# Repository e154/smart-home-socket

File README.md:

Автомат управления розетками/нагрузками
---------------------------------------

[Project site](https://e154.github.io/smart-home/) |
[Server](https://github.com/e154/smart-home/) |
[Configurator](https://github.com/e154/smart-home-configurator/) |
[Node](https://github.com/e154/smart-home-node/) |
[Development Tools](https://github.com/e154/smart-home-tools/) |
[Smart home Socket](https://github.com/e154/smart-home-socket/)

##### Функции
    Контроль температуры силового блока
    Включение/Выключения по команде управляющего сервера
    Контроль наличия сети/фазы

##### Общение с сервером
    Общение происходит по линии связи rs485, с помощью модифицированного 
    протокола MODBUS ASCII

##### Поведение автомата

    состояния:
    включен/выключен

    температура:
    в пределах нормы
    за пределами нормы

    комманды консоли:
    запрос состояния
          температура
          фаза
          вкл/выкл
          максимальный предел температуры
    включить
    выключить

##### Список компонентов

    Qty Value            Device                  Package         Parts              Description          
    1                    CPOL-EUE2,5-6E          E2,5-6E         C12                POLARIZED CAPACITOR, 
    1                    LEDCHIPLED_0805         CHIPLED_0805    LED2               LED                  
    5                    M01NOSILK-KIT           1X01NS-KIT      J1, J2, J3, J6, J7 Header 1             
    3                    M01PTH_NO_SILK_YES_STOP 1X01_NO_SILK    J4, J5, TEMP       Header 1             
    1                    MA03-2                  MA03-2          ISP                PIN HEADER           
    4                    MA04-1                  MA04-1          SV1, SV2, SV3, SV5 PIN HEADER           
    1   0.05mF           C-EUC0805               C0805           C6                 CAPACITOR, European  
    5   0.1              C-EUC0805               C0805           C1, C4, C5, C7, C8 CAPACITOR, European  
    2   10K              R-EU_M0805              M0805           R8, R12            RESISTOR, European s 
    3   10K              R-EU_R0805              R0805           R1, R13, R14       RESISTOR, European s 
    1   120R             R-EU_R0805              R0805           R17                RESISTOR, European s 
    1   16MHz            CRYSTALHC49U70          HC49U70         Q1                 CRYSTAL              
    1   1K               R-EU_M0805              M0805           R10                RESISTOR, European s 
    1   1K               R-EU_M1206              M1206           R9                 RESISTOR, European s 
    1   1K               R-EU_R0805              R0805           R2                 RESISTOR, European s 
    2   22p              C-EUC0805               C0805           C2, C3             CAPACITOR, European  
    3   330              R-EU_M0805              M0805           R3, R4, R5         RESISTOR, European s 
    1   560K             R-EU_M0805              M0805           R7                 RESISTOR, European s 
    2   560R             R-EU_R0805              R0805           R15, R16           RESISTOR, European s 
    1   78L05Z           78L05Z                  TO92            IC3                Positive VOLTAGE REG 
    2   82K              R-EU_0309/10            0309/10         R6, R11            RESISTOR, European s 
    1   AZ8-FORM-C       AZ8-FORM-C              AZ8             K1                 MINIATURE PC BOARD R 
    2   BC847            NPNSOT23                SOT-23          T2, T3             NPN TRANSISTOR       
    1   BT138-V          BT138-V                 TO220BV         T1                 TRIAC                
    2   DBDB101G         DBDB101G                DB              B1, B2             Single Phase 1.0 AMP 
    1   F/TMB            F/TMB                   F/TMB           SG1                BUZZER Source: Buerk 
    1   MAX481CSA        MAX481CSA               SO08            IC2                RS485 TRANSEIVER     
    1   MEGA48/88/168-AU MEGA48/88/168-AU        TQFP32-08       IC1                                     
    2   MKDSN1,5/2-5,08  MKDSN1,5/2-5,08         MKDSN1,5/2-5,08 X1, X2             MKDSN 1,5/ 2-5,08 Pr 
    1   MOC3031M         MOC3031M                DIL06           OK2                6-Pin DIP Zero-Cross 
    2   PC817            PC817                   DIL04           OK1, OK3           SHARP OPTO COUPLER   

##### Фоты

#### LICENSE

Smart home socket is licensed under the [MIT License (MIT)](https://github.com/e154/smart-home-socket/blob/master/LICENSE).

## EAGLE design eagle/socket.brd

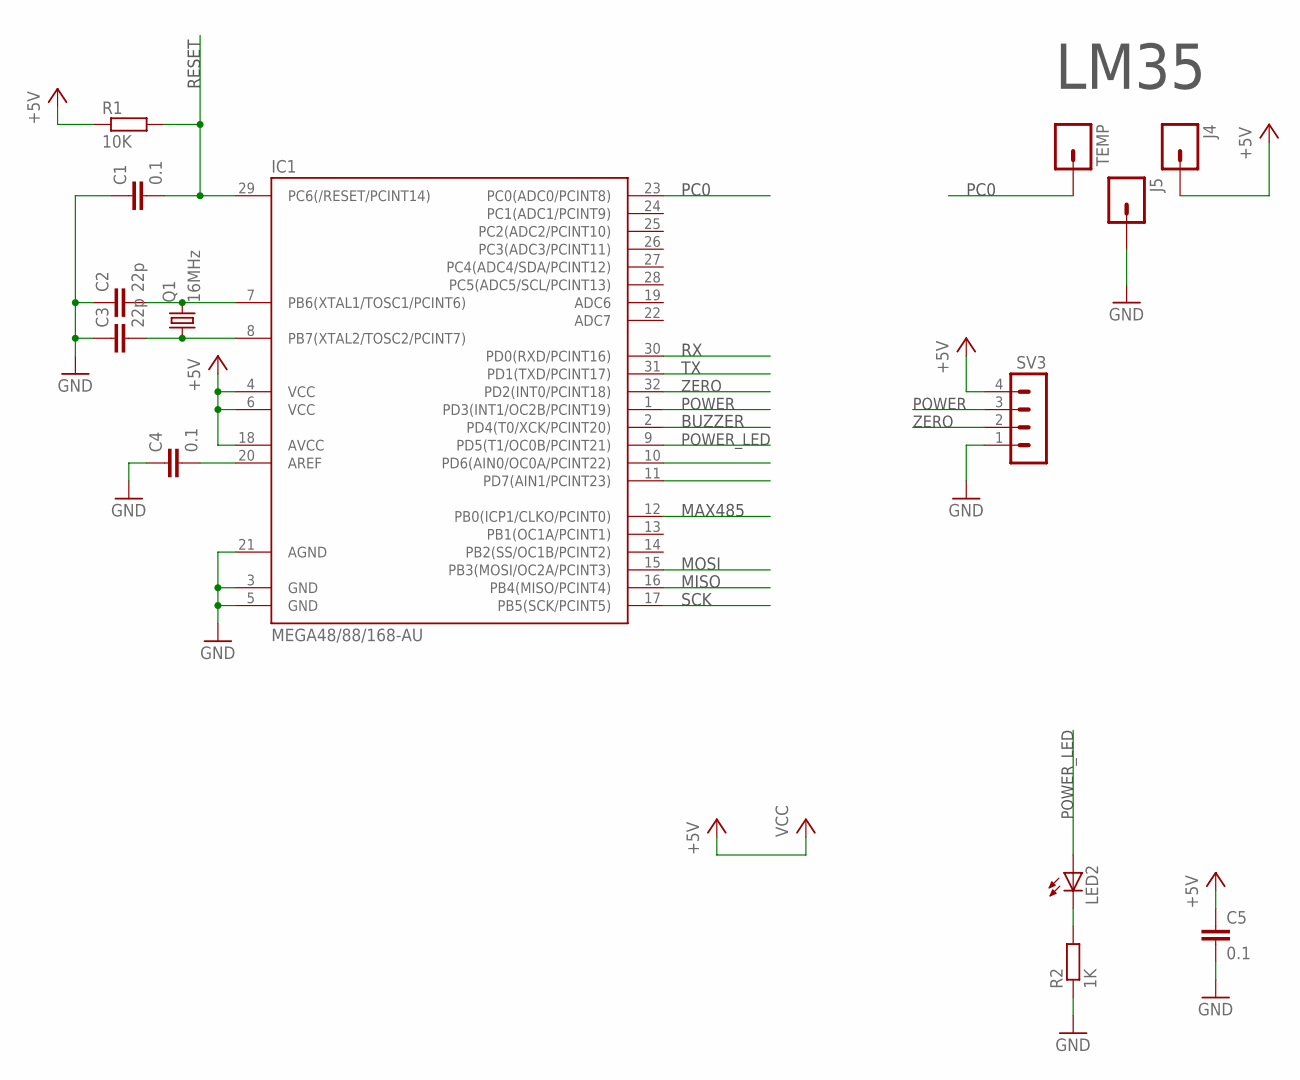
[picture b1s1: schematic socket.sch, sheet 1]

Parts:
C1, C4, C5: 0.1; C0805
C2, C3: 22p; C0805
IC1: MEGA48/88/168-AU; TQFP32-08
J4, J5: M01PTH_NO_SILK_YES_STOP; 1X01_NO_SILK
LED2: LEDCHIPLED_0805; CHIPLED_0805
Q1: 16MHz; HC49U70
R1: 10K; R0805
R2: 1K; R0805
SV3: MA04-1
TEMP: M01PTH_NO_SILK_YES_STOP; 1X01_NO_SILK

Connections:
+5V: C5.1, IC1.4 (VCC), IC1.6 (VCC), IC1.18 (AVCC), J4.1, R1.1, SV3.4; also elsewhere on the board
BUZZER: IC1.2 (PD4(T0/XCK/PCINT20)); also elsewhere on the board
GND: C1.1, C2.1, C3.1, C4.1, C5.2, IC1.3 (GND), IC1.5 (GND), IC1.21 (AGND), J5.1, R2.1, SV3.1; also elsewhere on the board
MISO: IC1.16 (PB4(MISO/PCINT4)); also elsewhere on the board
MOSI: IC1.15 (PB3(MOSI/OC2A/PCINT3)); also elsewhere on the board
unnamed: C4.2, IC1.20 (AREF)
unnamed: C2.2, IC1.7 (PB6(XTAL1/TOSC1/PCINT6)), Q1.2
unnamed: C3.2, IC1.8 (PB7(XTAL2/TOSC2/PCINT7)), Q1.1
unnamed: LED2.C, R2.2
PB0: IC1.12 (PB0(ICP1/CLKO/PCINT0)); also elsewhere on the board
PC0: IC1.23 (PC0(ADC0/PCINT8)), TEMP.1
PD3: IC1.1 (PD3(INT1/OC2B/PCINT19)), SV3.3
PD4: IC1.32 (PD2(INT0/PCINT18)), SV3.2
POWER_LED: IC1.9 (PD5(T1/OC0B/PCINT21)), LED2.A
RESET: C1.2, IC1.29 (PC6(/RESET/PCINT14)), R1.2; also elsewhere on the board
RX: IC1.30 (PD0(RXD/PCINT16)); also elsewhere on the board
SCK: IC1.17 (PB5(SCK/PCINT5)); also elsewhere on the board
TX: IC1.31 (PD1(TXD/PCINT17)); also elsewhere on the board

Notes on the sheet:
RESET
SCK
MISO
MOSI
MAX485
PC0
BUZZER
POWER
ZERO
LM35
POWER_LED

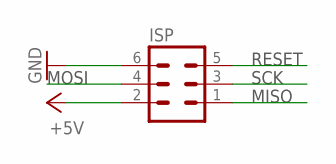
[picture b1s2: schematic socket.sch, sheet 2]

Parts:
ISP: MA03-2

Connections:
+5V: ISP.2; also elsewhere on the board
GND: ISP.6; also elsewhere on the board
MISO: ISP.1; also elsewhere on the board
MOSI: ISP.4; also elsewhere on the board
RESET: ISP.5; also elsewhere on the board
SCK: ISP.3; also elsewhere on the board

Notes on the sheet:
RESET
SCK
MISO
MOSI

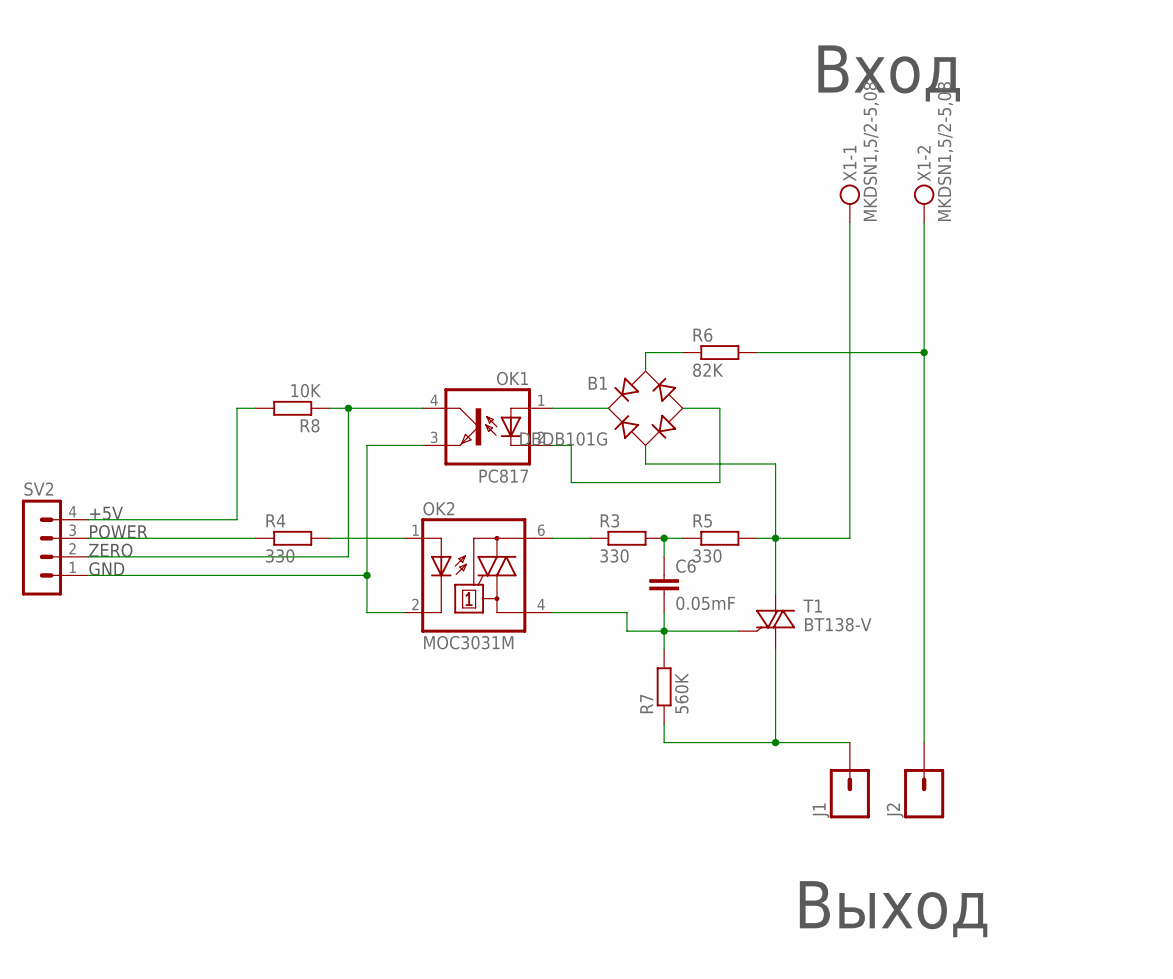
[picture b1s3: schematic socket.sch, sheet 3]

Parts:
B1: DBDB101G; DB
C6: 0.05mF; C0805
J1, J2: M01NOSILK-KIT; 1X01NS-KIT
OK1: PC817; DIL04
OK2: MOC3031M; DIL06
R3, R4, R5: 330; M0805
R6: 82K; 0309/10
R7: 560K; M0805
R8: 10K; M0805
SV2: MA04-1
T1: BT138-V; TO220BV
X1: MKDSN1,5/2-5,08

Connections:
unnamed: B1.AC2, R5.2, T1.T2 (A2), X1.1
unnamed: OK2.6 (A2), R3.1
unnamed: C6.2, OK2.4 (A1), R7.2, T1.G
unnamed: J1.1, R7.1, T1.T1 (A1)
unnamed: OK2.1 (A), R4.2
unnamed: J2.1, R6.2, X1.2
unnamed: C6.1, R3.2, R5.1
unnamed: B1.+, OK1.1 (A)
unnamed: B1.-, OK1.2 (C)
unnamed: B1.AC1, R6.1
unnamed: R8.2, SV2.4
unnamed: OK1.3 (EMIT), OK2.2 (C), SV2.1
POWER: R4.1, SV2.3
ZERO: OK1.4 (COL), R8.1, SV2.2

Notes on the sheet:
Вход
Выход
ZERO
POWER
+5V
GND

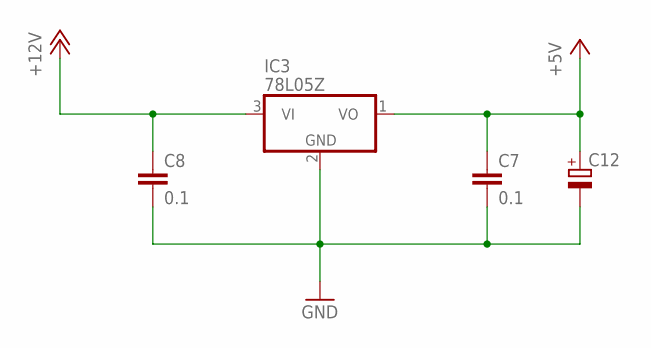
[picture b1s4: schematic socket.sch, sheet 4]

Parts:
C7, C8: 0.1; C0805
C12: CPOL-EUE2,5-6E; E2,5-6E
IC3: 78L05Z; TO92

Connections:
+5V: C7.1, C12.+, IC3.1 (VO); also elsewhere on the board
+12V: C8.1, IC3.3 (VI); also elsewhere on the board
GND: C7.2, C8.2, C12.-, IC3.2 (GND); also elsewhere on the board

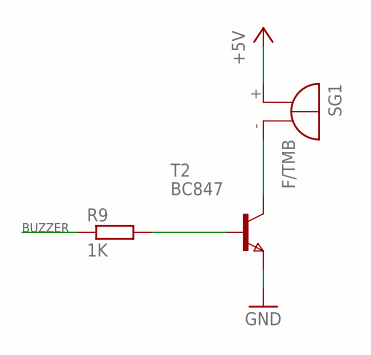
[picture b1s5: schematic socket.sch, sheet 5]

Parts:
R9: 1K; M1206
SG1: F/TMB
T2: BC847; SOT-23

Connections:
+5V: SG1.+; also elsewhere on the board
BUZZER: R9.1; also elsewhere on the board
GND: T2.2 (E); also elsewhere on the board
unnamed: R9.2, T2.3 (B)
SPEAKER-: SG1.-, T2.1 (C)

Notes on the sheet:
BUZZER

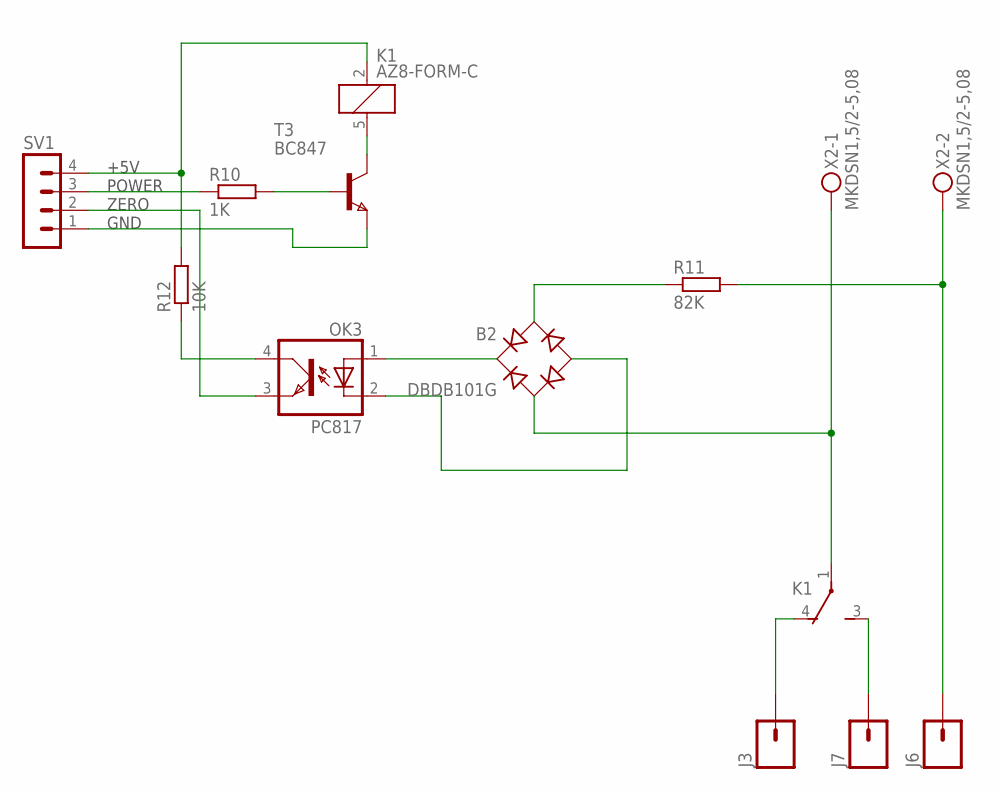
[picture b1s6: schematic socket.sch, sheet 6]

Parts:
B2: DBDB101G; DB
J3, J6, J7: M01NOSILK-KIT; 1X01NS-KIT
K1: AZ8-FORM-C; AZ8
OK3: PC817; DIL04
R10: 1K; M0805
R11: 82K; 0309/10
R12: 10K; M0805
SV1: MA04-1
T3: BC847; SOT-23
X2: MKDSN1,5/2-5,08

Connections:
unnamed: R10.1, SV1.3
unnamed: R10.2, T3.3 (B)
unnamed: K1.5 (2), T3.1 (C)
unnamed: K1.2 (1), R12.2, SV1.4
unnamed: J7.1, K1.3 (S)
unnamed: J3.1, K1.4 (O)
unnamed: J6.1, R11.2, X2.2
unnamed: SV1.1, T3.2 (E)
unnamed: OK3.4 (COL), R12.1
unnamed: OK3.3 (EMIT), SV1.2
unnamed: B2.+, OK3.1 (A)
unnamed: B2.-, OK3.2 (C)
unnamed: B2.AC1, R11.1
unnamed: B2.AC2, K1.1, X2.1

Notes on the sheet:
+5V
POWER
ZERO
GND

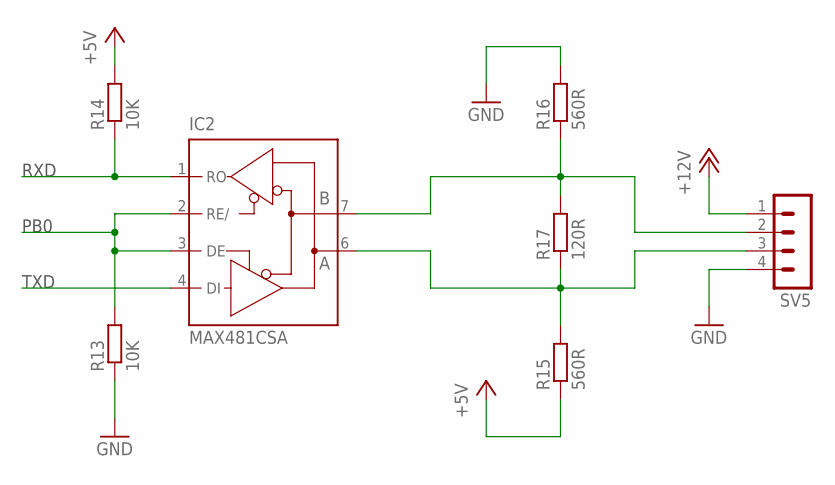
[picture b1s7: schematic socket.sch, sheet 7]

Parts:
IC2: MAX481CSA; SO08
R13, R14: 10K; R0805
R15, R16: 560R; R0805
R17: 120R; R0805
SV5: MA04-1

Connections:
+5V: IC2.8 (VCC), R14.2, R15.1; also elsewhere on the board
+12V: SV5.1; also elsewhere on the board
GND: IC2.5 (GND), R13.1, R16.2, SV5.4; also elsewhere on the board
unnamed: IC2.7 (B), R16.1, R17.2, SV5.2
unnamed: IC2.6 (A), R15.2, R17.1, SV5.3
PB0: IC2.2 (RE/), IC2.3 (DE), R13.2; also elsewhere on the board
RX: IC2.1 (RO), R14.1; also elsewhere on the board
TX: IC2.4 (DI); also elsewhere on the board

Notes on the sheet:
RXD
TXD
PB0

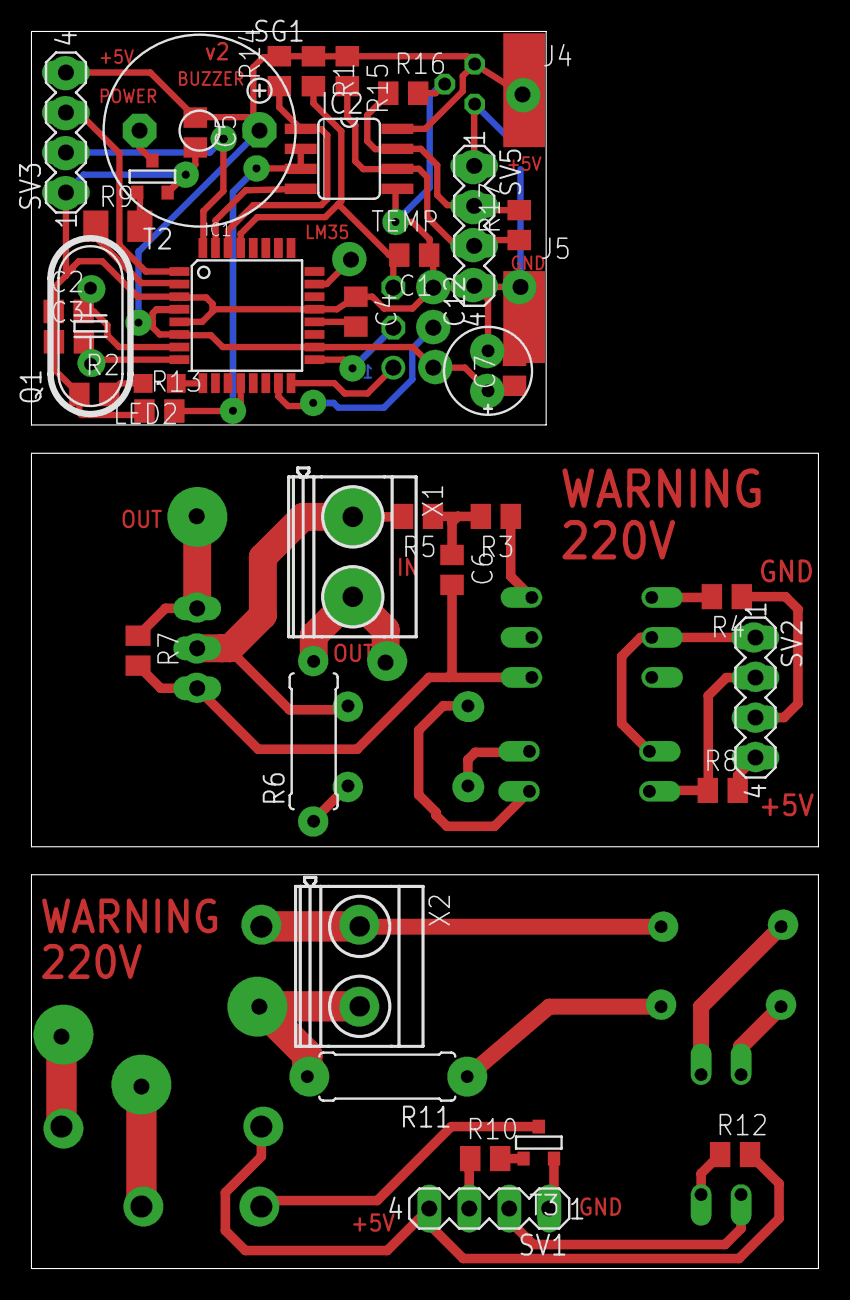
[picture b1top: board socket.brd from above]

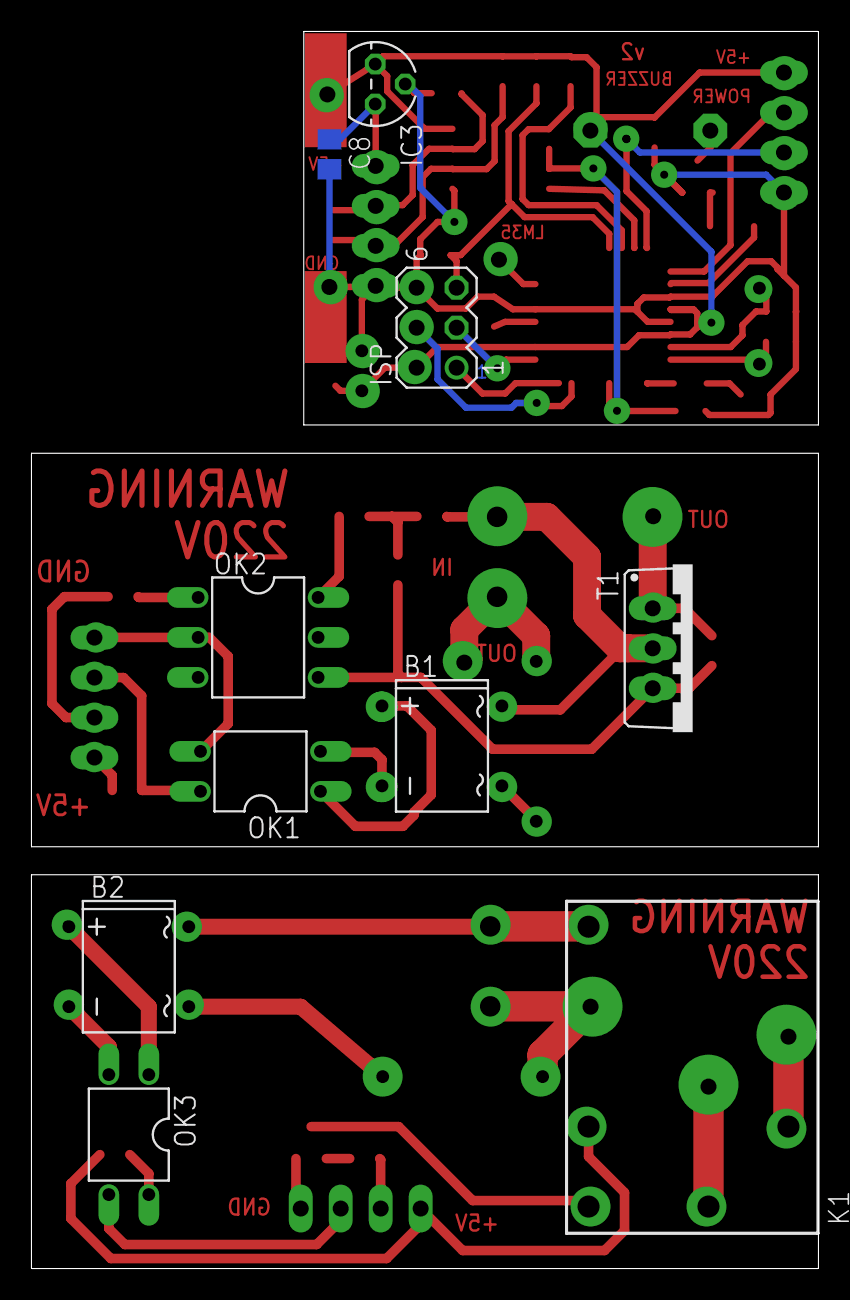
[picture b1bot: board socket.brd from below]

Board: 2 copper layers, 50.0 x 78.6 mm, 56 parts (10 on the bottom side), 51 nets.

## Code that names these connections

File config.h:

//
// Created by delta54 on 9/30/16.
//

#ifndef CMAKE_AVR_CONFIG_H
#define CMAKE_AVR_CONFIG_H

#include <avr/io.h>

#define BUZZER_PORT         PORTD
#define BUZZER_PIN          PD4
#define TOGGLE_PORT         PORTD
#define TOGGLE_PIN          PD3
#define PHAZE_PIN           PD2

#define TEMPER_PORT         PORTC
#define TEMPER_PIN          PC0

#define PWR_LED_PORT        PORTD
#define PWR_LED             PD5

#define MAX485_PORT         PORTB
#define MAX485_PIN          PB0
#define MAX_TEMP            1089 // 109C^

#define DEVICE_ADDRESS      0x01       /*!< Device address hex format. */

#endif //CMAKE_AVR_CONFIG_H

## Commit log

2016-10-29 bug fix
2016-11-05 eagle screenshot
2016-12-19 refactor
2017-01-26 travis
2017-02-12 add component list
2017-10-15 readme fix
2018-12-02 modbus
2018-12-02 smartbus
2018-12-02 fixes

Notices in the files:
parts and their libraries:
SparkFun-Connectors: Licensing: Creative Commons ShareAlike 4.0 International - https://creativecommons.org/licenses/by-sa/4.0
